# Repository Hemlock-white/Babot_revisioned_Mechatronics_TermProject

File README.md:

# BaBot through-hole adaptation

This repository develops a hand-assemblable version of [Johan Link's BaBot](https://github.com/JohanLink/BABOT), a three-servo robot that balances a ball using an infrared sensor array. It preserves the downloaded original material, the current PCB and mechanical working files, an Arduino sketch copy, and the superseded design experiments.

## Start here

| Folder | Contents |
| --- | --- |
| [`hardware/`](hardware/) | Working mechanical STL copied from the original download. |
| [`PCB/`](PCB/) | Current KiCad electronics, grouped purchase BOMs, routing/validation notes, and four-layer Base and two-layer Plate fabrication files. |
| [`software/`](software/) | Working Arduino sketch; currently byte-for-byte identical to the upstream `main.ino`. The [interactive software navigator](docs/BaBot_導覽.html) teaches its architecture and algorithms. |
| [`history/`](history/) | Earlier Base versions, two-layer routing experiments, and prior circuit notes. |
| [`original/`](original/) | Untouched upstream sketch/license plus original PCBWay, mechanical, schematic, and saved-page downloads. |
| [`docs/`](docs/) | [Development log](docs/dev_log.md), illustrated [original circuit lesson](docs/electronics_original.html) and [current THT circuit lesson](docs/electronics_tht.html), their Markdown sources, and a blank `hardware_explained.md`. |

Open the [four-layer Base KiCad project](PCB/KiCad/BaBot_Base_THT_4067_Module.kicad_pro) or the [two-layer Plate KiCad project](PCB/KiCad/BaBot_Plate_THT.kicad_pro) in KiCad 10. Keep their `BaBot_THT.pretty` footprint folder, symbol library, and library tables beside the project files. Use the [Base BOM](PCB/KiCad/BaBot_Base_THT_4067_Module_BOM.csv) and [Plate BOM](PCB/KiCad/BaBot_Plate_THT_BOM.csv) to plan one or five assemblies and mark parts on hand. The [Base Gerber ZIP](PCB/fabrication/BaBot_Base_THT_4layer_Gerbers.zip) is the four-layer fabrication package; read its [order notes](PCB/fabrication/BaBot_Base_THT_4layer/ORDER_NOTES.md) before ordering.

The Base and Plate in `PCB/` are routed, and each board's last PCB DRC found **0 violations and 0 unconnected items**. The Base's 2 A servo-power assumption and 1 oz inner-copper recommendation still need confirmation against the chosen servos and mechanical assembly. The corrected Plate [Gerber and drill ZIP](PCB/fabrication/plate_tht/BaBot_Plate_THT_2layer_Gerbers.zip) has nonempty mask plots on both sides; read its [fabrication notes](PCB/fabrication/plate_tht/README.md) before ordering. The earlier Plate export with empty masks and no drills, and the unfinished two-layer Base, are preserved in `history/`.

The software folder is currently a copy for future changes. Open the [BaBot software navigator](docs/BaBot_導覽.html) for a linked code editor, five flowcharts, and theory exercises. The self-contained [original](docs/electronics_original.html) and [THT](docs/electronics_tht.html) circuit lessons provide schematics and interactive examples. Their source guides and HTML builders are in `docs/`. Earlier Base/Plate circuit notes remain accessible in `history/notes/`.

## Credit and provenance

Original BaBot design and firmware: **Johan Link**, [BABOT GitHub repository](https://github.com/JohanLink/BABOT), [BaBot project site](https://ba-bot.com/), and [build article](https://www.hackster.io/johanlinkemail/babot-build-your-own-ball-balancing-robot-2c1a5a). The upstream repository states a **Creative Commons Attribution-NonCommercial 4.0** license; its original license is preserved in [`original/upstream/BABOT-main/LICENSE`](original/upstream/BABOT-main/LICENSE). Original PCBWay downloads and reference captures are identified in [`original/README.md`](original/README.md). This repository's local commits reconstruct development milestones from available files and KiCad snapshots; their commit dates are import dates, not claims about when the earlier engineering work originally happened.

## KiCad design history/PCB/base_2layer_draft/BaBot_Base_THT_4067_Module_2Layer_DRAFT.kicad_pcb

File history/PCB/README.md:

# Superseded PCB work

`initial_THT_Base/` preserves the first Base conversion, before the multiplexer module and trimmer changes. The early state is also represented by the second commit in this repository.

`base_2layer_draft/` preserves the later two-layer Base attempt. It is **not fabrication-ready**: the last recorded DRC had six signal connections and one ground connection open. `base_2layer_trials/` contains intermediate routing experiments. Open these only as historical design files, not as the current Base.

`kicad_auto_history.tar.gz` is an archive of KiCad's local saved snapshots from the pre-reorganization workspace. It is kept as a recovery record; the root Git commits provide the curated project timeline.

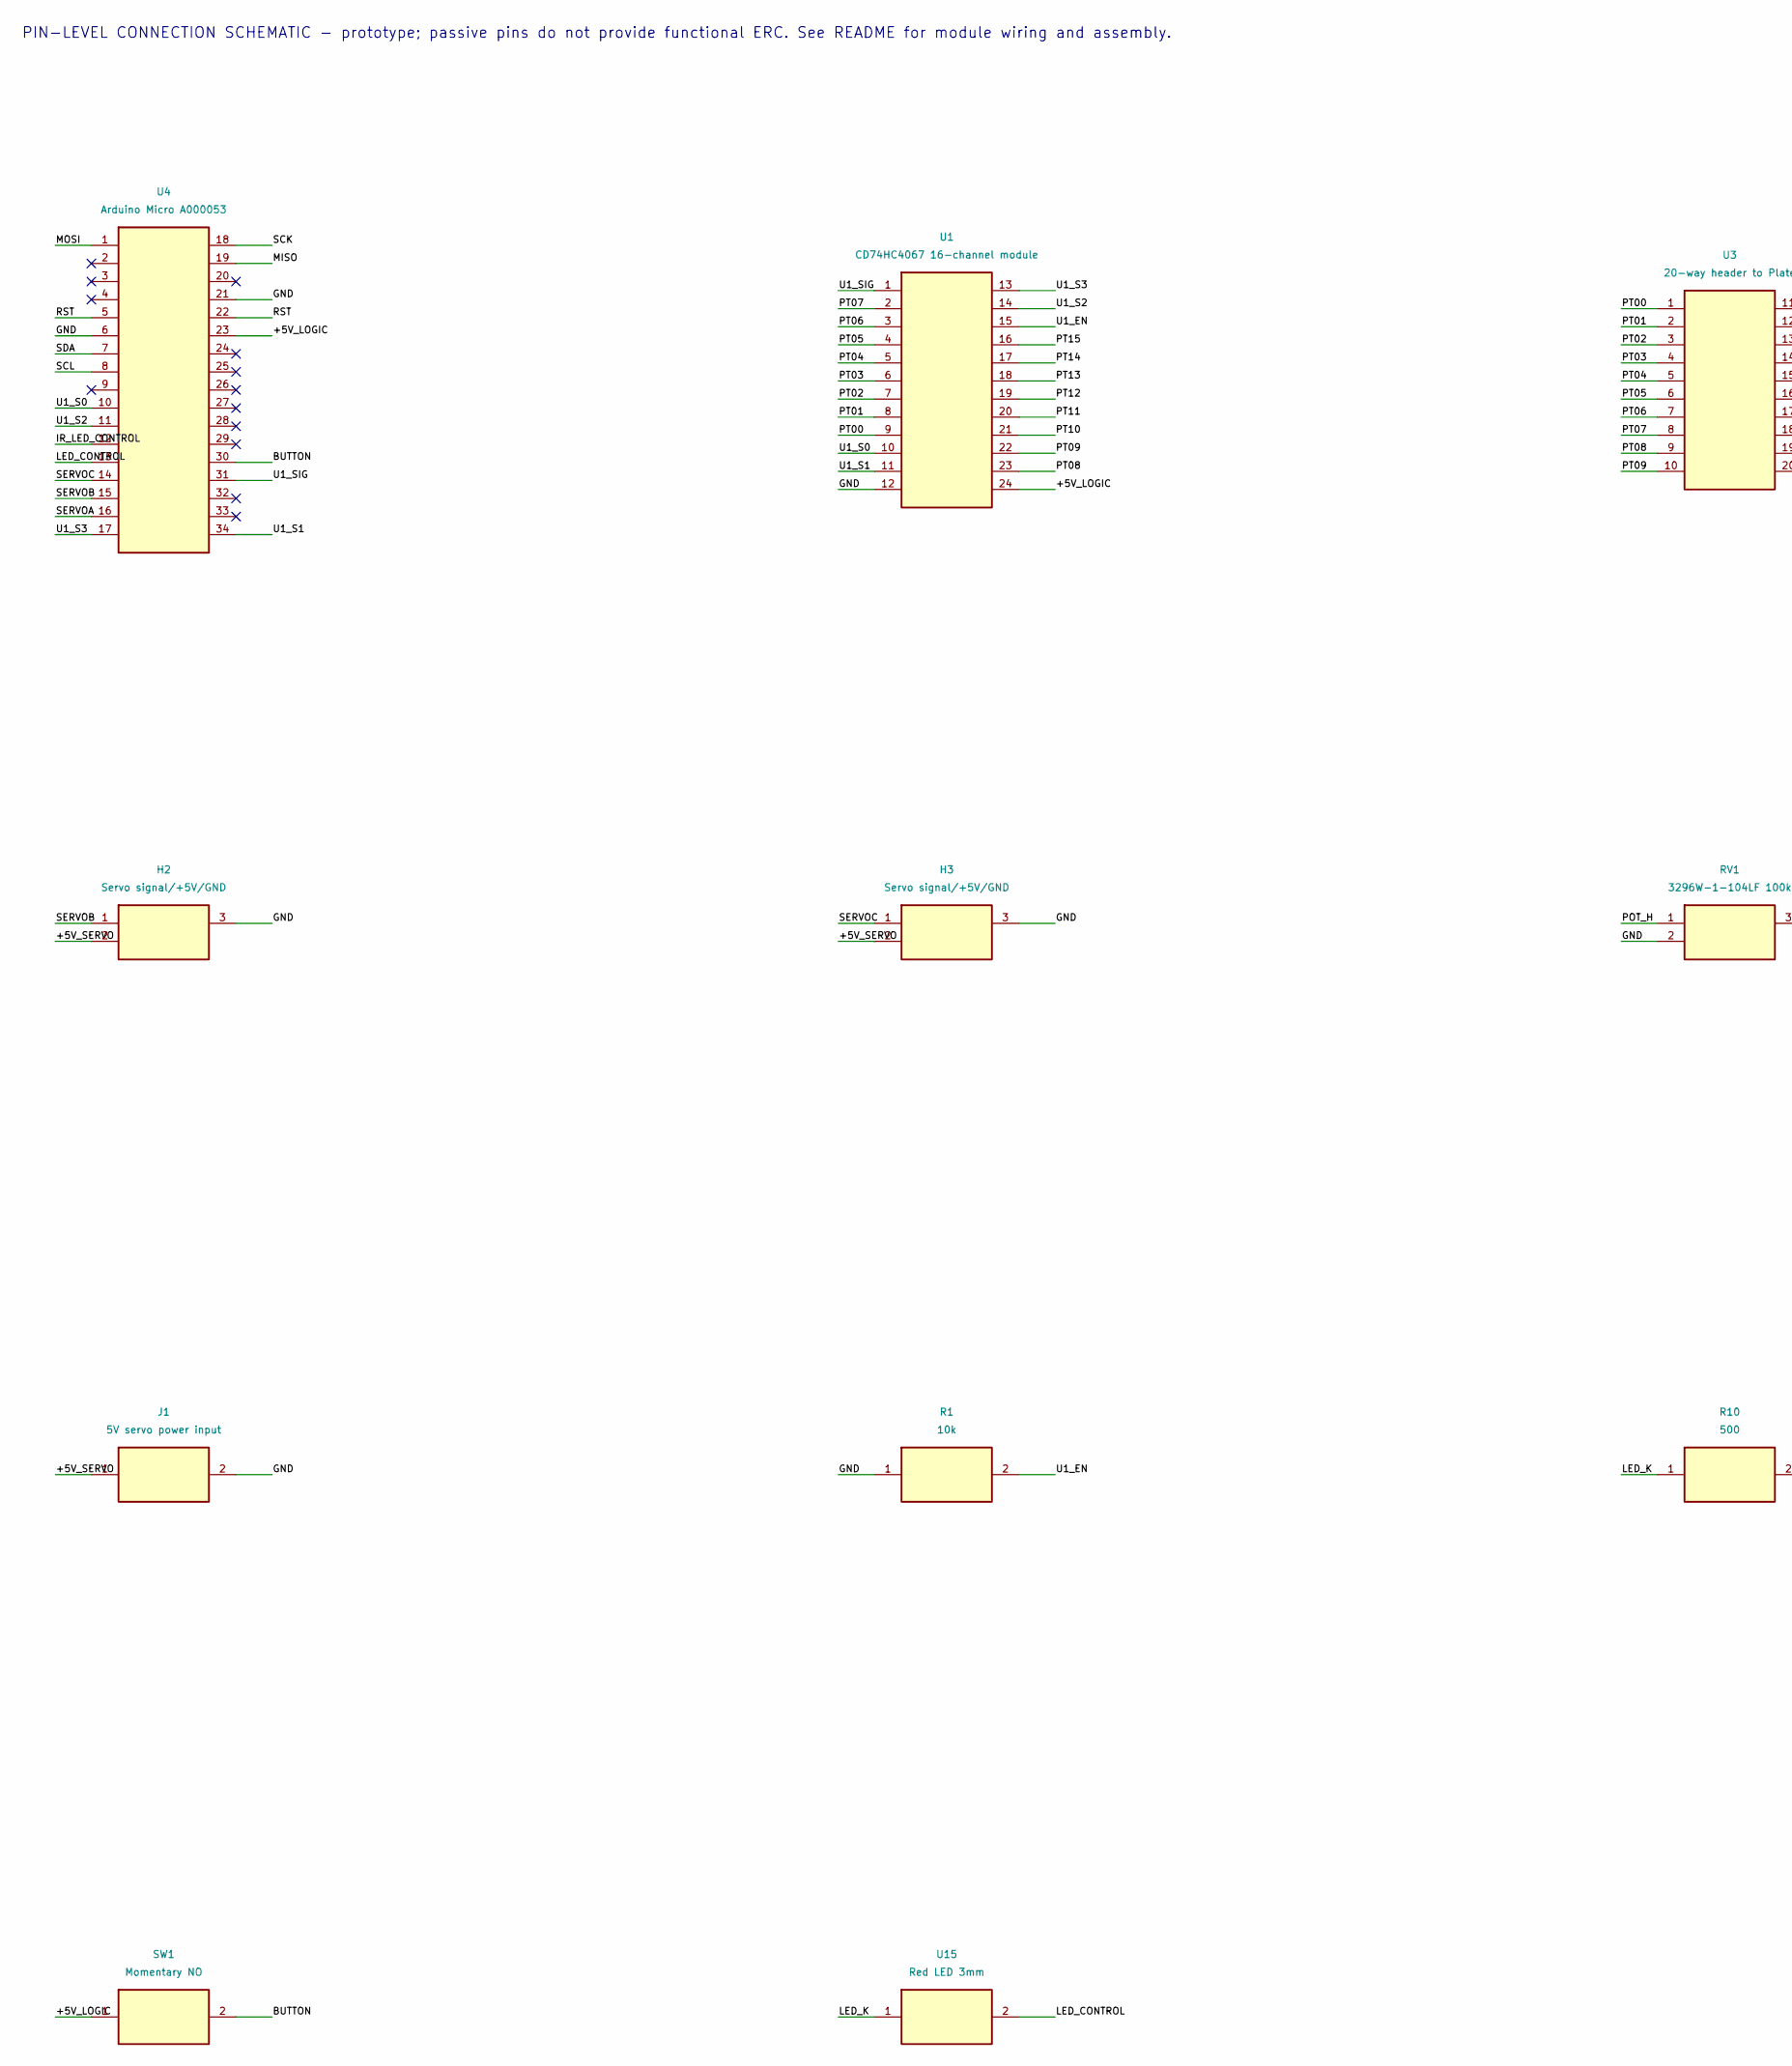
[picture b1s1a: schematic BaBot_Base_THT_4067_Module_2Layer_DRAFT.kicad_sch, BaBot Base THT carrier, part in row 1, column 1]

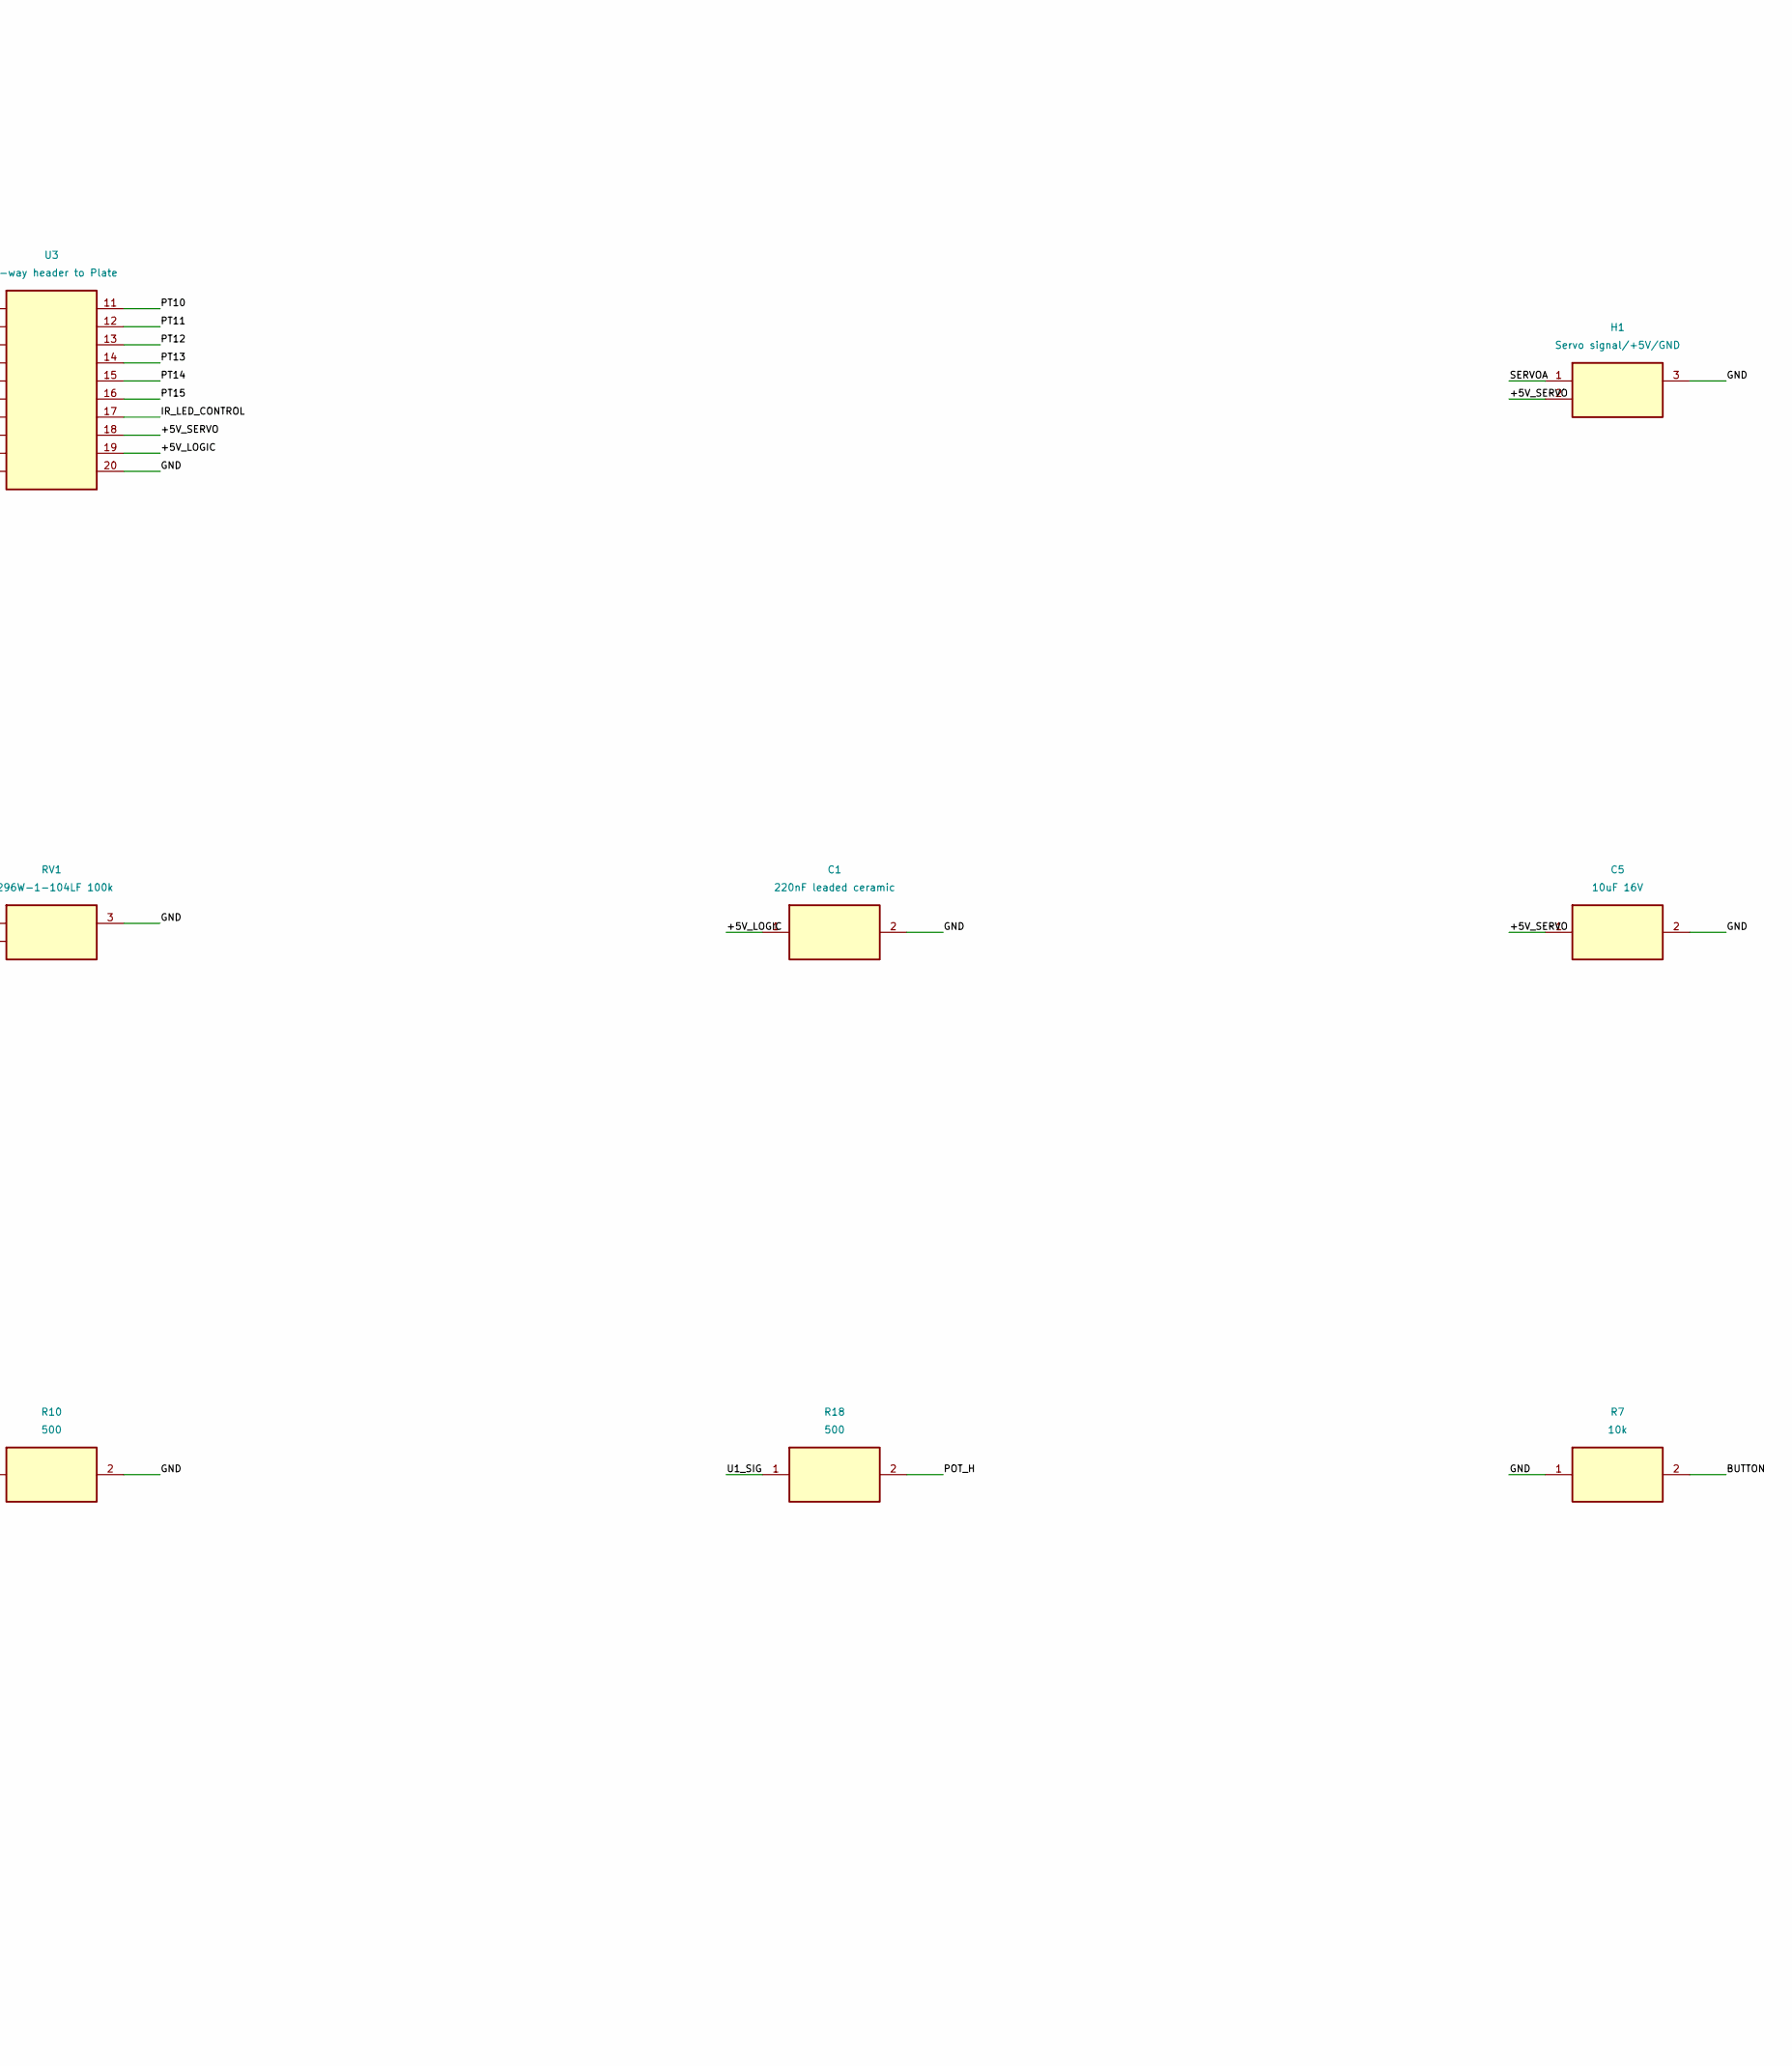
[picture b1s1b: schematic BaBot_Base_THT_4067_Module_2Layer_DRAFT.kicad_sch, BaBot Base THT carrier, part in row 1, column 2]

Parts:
C1: 220nF leaded ceramic; Ceramic_5mm
C5: 10uF 16V; Electrolytic_5mm
H1: Servo signal/+5V/GND; Original_Base_H1
H2: Servo signal/+5V/GND; Original_Base_H2
H3: Servo signal/+5V/GND; Original_Base_H3
J1: 5V servo power input; Power_Terminal
R1, R7: 10k; Axial_R_10.16
R10, R18: 500; Axial_R_10.16
RV1: 3296W-1-104LF 100k; Potentiometer_Bourns_3296W_Vertical
SW1: Momentary NO; Pushbutton_6mm
U1: CD74HC4067 16-channel module; CD74HC4067_Module_2Layer
U3: 20-way header to Plate; Header20
U4: Arduino Micro A000053; Arduino_Micro_A000053
U15: Red LED 3mm; LED_3mm

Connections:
+5V_LOGIC: C1.1, SW1.1, U1.24, U3.19, U4.23
+5V_SERVO: C5.1, H1.2, H2.2, H3.2, J1.1, U3.18
BUTTON: R7.2, SW1.2, U4.30
GND: C1.2, C5.2, H1.3, H2.3, H3.3, J1.2, R1.1, R7.1, R10.2, RV1.2, RV1.3, U1.12, U3.20, U4.6, U4.21
IR_LED_CONTROL: U3.17, U4.12
LED_CONTROL: U4.13, U15.2
LED_K: R10.1, U15.1
MISO: U4.19
MOSI: U4.1
POT_H: R18.2, RV1.1
PT00: U1.9, U3.1
PT01: U1.8, U3.2
PT02: U1.7, U3.3
PT03: U1.6, U3.4
PT04: U1.5, U3.5
PT05: U1.4, U3.6
PT06: U1.3, U3.7
PT07: U1.2, U3.8
PT08: U1.23, U3.9
PT09: U1.22, U3.10
PT10: U1.21, U3.11
PT11: U1.20, U3.12
PT12: U1.19, U3.13
PT13: U1.18, U3.14
PT14: U1.17, U3.15
PT15: U1.16, U3.16
RST: U4.5, U4.22
SCK: U4.18
SCL: U4.8
SDA: U4.7
SERVOA: H1.1, U4.16
SERVOB: H2.1, U4.15
SERVOC: H3.1, U4.14
U1_EN: R1.2, U1.15
U1_S0: U1.10, U4.10
U1_S1: U1.11, U4.34
U1_S2: U1.14, U4.11
U1_S3: U1.13, U4.17
U1_SIG: R18.1, U1.1, U4.31

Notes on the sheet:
PIN-LEVEL CONNECTION SCHEMATIC - prototype; passive pins do not provide functional ERC. See README for module wiring and assembly.

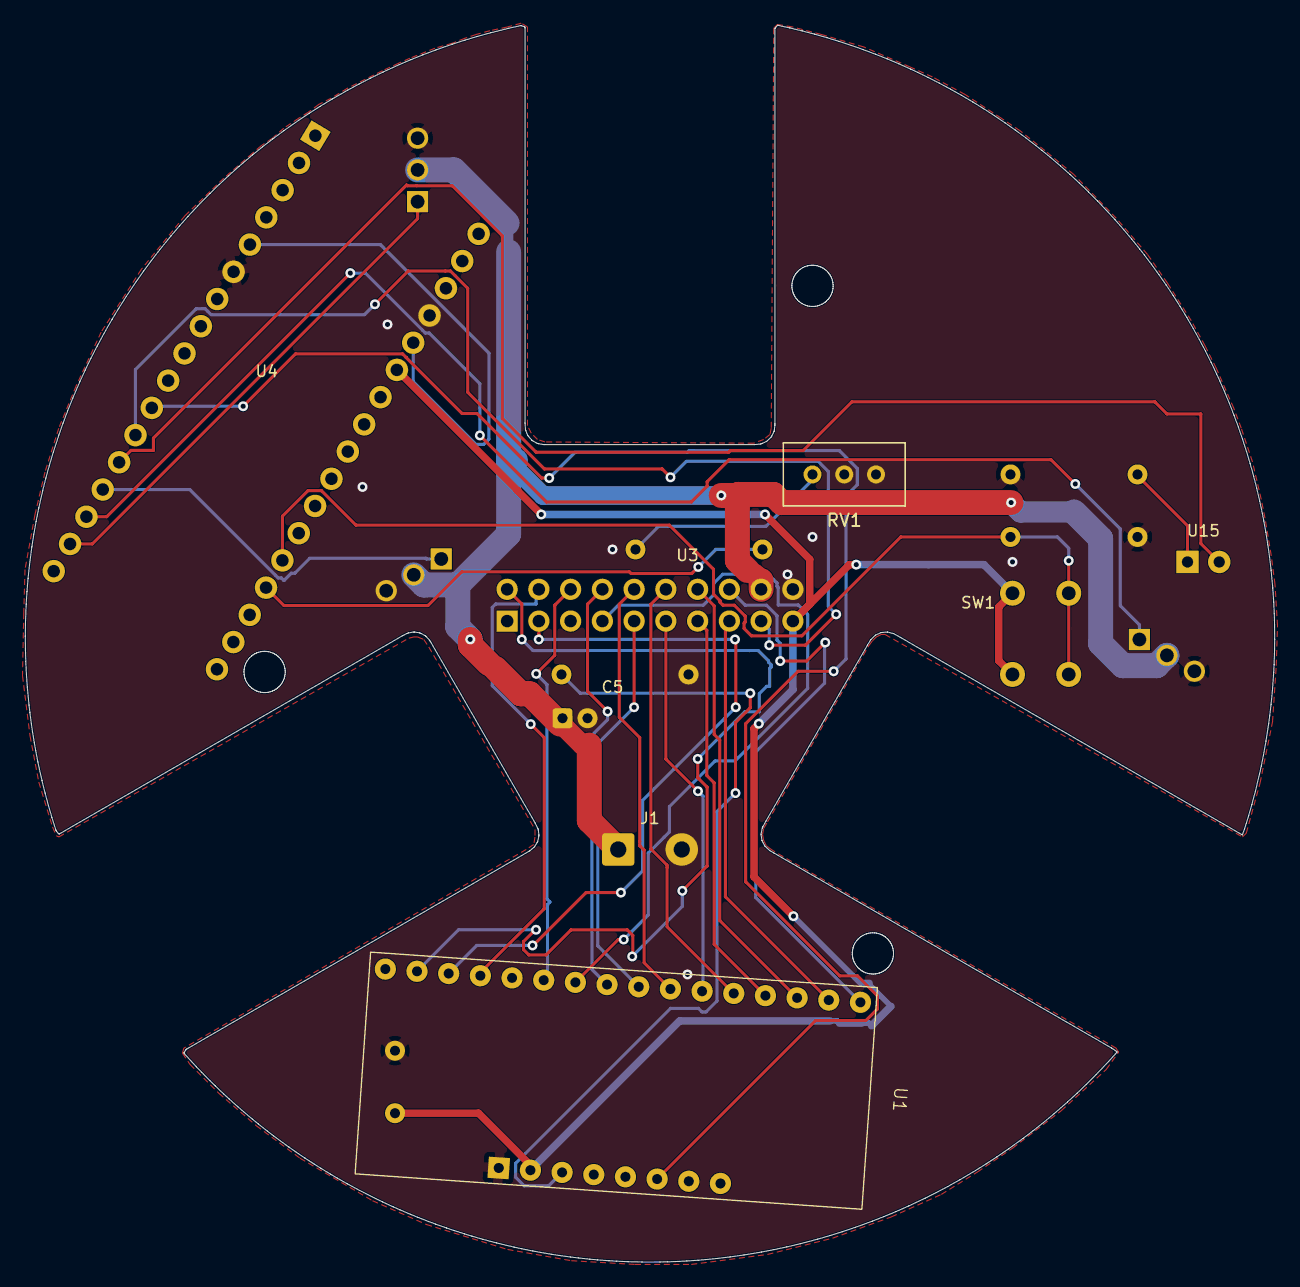
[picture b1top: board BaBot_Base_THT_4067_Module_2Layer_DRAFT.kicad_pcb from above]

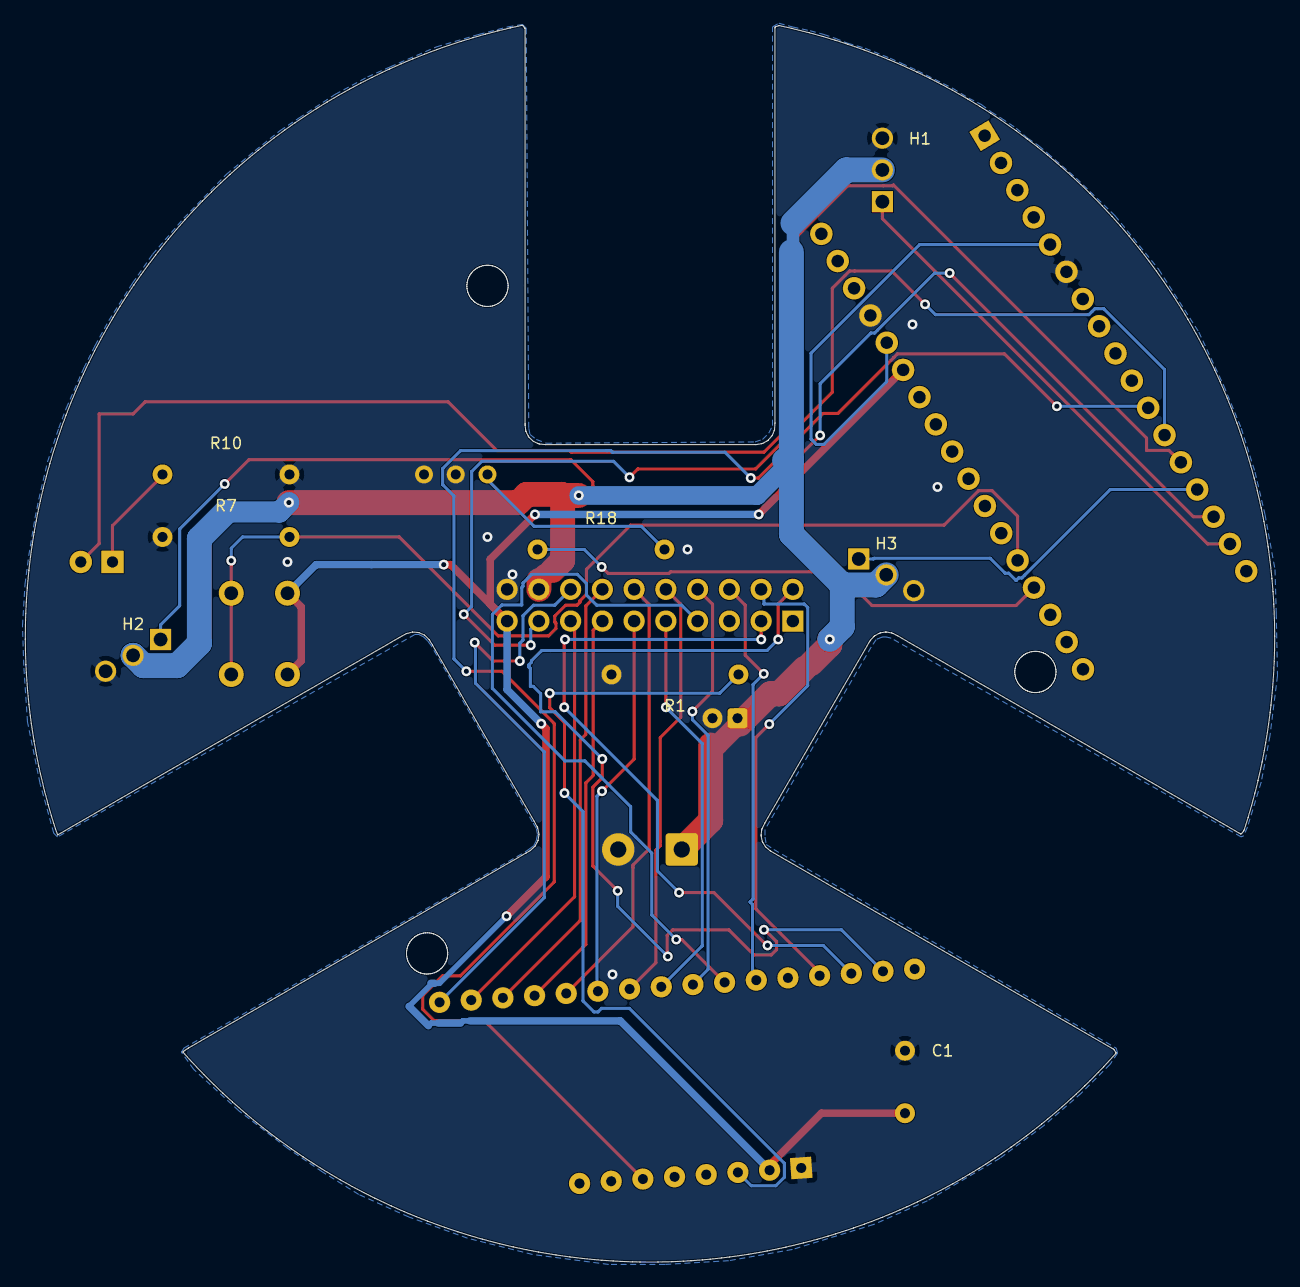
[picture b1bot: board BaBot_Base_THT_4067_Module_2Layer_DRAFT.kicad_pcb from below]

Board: 2 copper layers, 99.9 x 98.9 mm, 16 parts (8 on the bottom side), 34 nets.

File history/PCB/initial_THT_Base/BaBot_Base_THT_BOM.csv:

Reference,Value,Footprint,Side,Purpose,Supplier Link
U4,Arduino Micro A000053,Arduino_Micro_A000053,F,Preassembled ATmega32U4 module; USB logic supply and programming,https://shopee.tw/search?keyword=Arduino%20Micro%20A000053%2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
U2,MIKROE-2332 DIGI POT 2,DIGI_POT_2_MIKROE2332,F,"Dedicated TPL0501 socket, both supply pins 5 V; analog terminals wired to J2",https://s.taobao.com/search?q=CD74HC4067E%20CD74HC4067E%20DI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
U1,CD74HC4067E,DIP24_Socket,F,Original circuit; footprint converted or retained,https://s.taobao.com/search?q=CD74HC4067E%20CD74HC4067E%20DI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
U3,20-way header to Plate,Header20,F,Original circuit; footprint converted or retained,https://www.lcsc.com/product-detail/C54803349.html
H1,Servo signal/+5V/GND,Original_Base_H1,B,Original circuit; footprint converted or retained,https://s.taobao.com/search?q=PZ254V-11-03P%202.54mm%201x3%2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
H2,Servo signal/+5V/GND,Original_Base_H2,B,Original circuit; footprint converted or retained,https://s.taobao.com/search?q=PZ254V-11-03P%202.54mm%201x3%2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
H3,Servo signal/+5V/GND,Original_Base_H3,B,Original circuit; footprint converted or retained,https://s.taobao.com/search?q=PZ254V-11-03P%202.54mm%201x3%2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
R1,10k,Axial_R_10.16,B,Original circuit; footprint converted or retained,https://www.lcsc.com/product-detail/C2903232.html
R7,10k,Axial_R_10.16,B,Original circuit; footprint converted or retained,https://www.lcsc.com/product-detail/C2903232.html
R10,500,Axial_R_10.16,B,Original circuit; footprint converted or retained,https://www.lcsc.com/product-detail/C1370878.html
R18,500,Axial_R_10.16,B,Original circuit; footprint converted or retained,https://www.lcsc.com/product-detail/C1370878.html
C1,220nF leaded ceramic,Ceramic_5mm,B,Original circuit; footprint converted or retained,https://shopee.tw/search?keyword=220nF%200.22uF%20ceramic%20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
C5,10uF 16V,Electrolytic_5mm,F,Servo rail bulk capacitor; original value retained,https://www.lcsc.com/product-detail/C442560.html
SW1,Momentary NO,Pushbutton_6mm,F,Original active-high mode button; standard THT switch,https://shopee.tw/search?keyword=6x6mm%20tactile%20push%20bu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
U15,Red LED 3mm,LED_3mm,F,"Original LED function; KiCad pin 1 cathode, pin 2 anode",https://shopee.tw/search?keyword=3mm%20red%20LED%20through%2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
J1,5V servo power input,Power_Terminal,F,External regulated 5 V servo supply; separate from Micro USB logic supply,https://www.lcsc.com/product-detail/C5183929.html
J2,TPL0501 H W L,Header_1x03,F,"Three short wires to Click screw terminals H, W, L respectively",https://s.taobao.com/search?q=2.54mm%201x3%20straight%20male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
